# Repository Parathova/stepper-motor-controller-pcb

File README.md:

# stepper-motor-controller-pcb

## Overview

Designed a custom PCB in KiCad to control a NEMA-17
stepper motor through an A4988 driver.

The design includes:

- Arduino Uno headers
- A4988 driver interface
- Push-button inputs
- Status LEDs
- Power filtering capacitor
- Motor output connections

## Tools

- KiCad
- Arduino Uno
- A4988 Stepper Driver

## Features

- Controls NEMA-17 stepper motor
- Button-based user interface
- Modular driver design
- Custom PCB layout

## Schematic

## PCB Layout

## 3D Render

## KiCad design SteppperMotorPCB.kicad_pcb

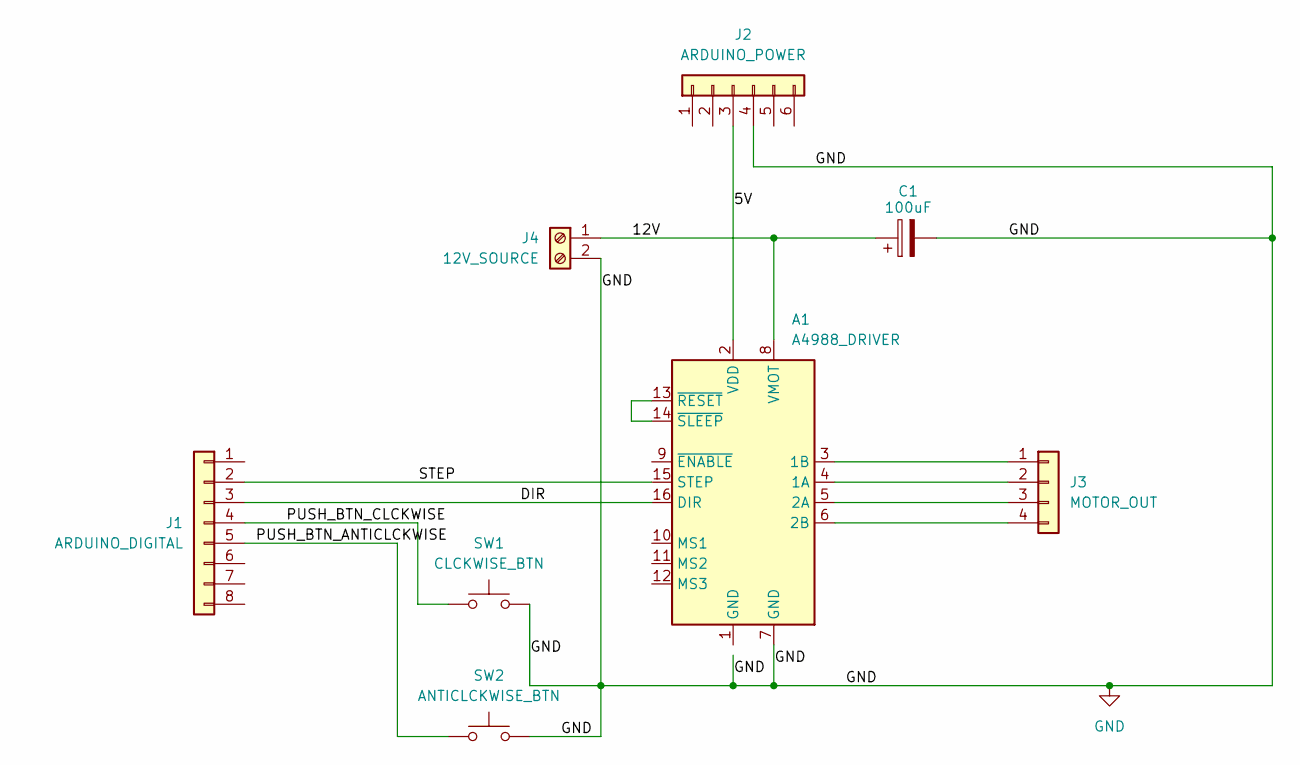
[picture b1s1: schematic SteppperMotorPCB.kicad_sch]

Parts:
A1: A4988_DRIVER; Pololu_Breakout-16_15.2x20.3mm
C1: 100uF; CP_Radial_D8.0mm_P3.50mm
J1: ARDUINO_DIGITAL; PinHeader_1x08_P2.54mm_Vertical
J2: ARDUINO_POWER; PinHeader_1x06_P2.54mm_Vertical
J3: MOTOR_OUT; PinHeader_1x04_P2.54mm_Vertical
J4: 12V_SOURCE; TerminalBlock_Phoenix_MKDS-1,5-2-5.08_1x02_P5.08mm_Horizont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
SW1: CLCKWISE_BTN; SW_PUSH_6mm
SW2: ANTICLCKWISE_BTN; SW_PUSH_6mm

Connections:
/5V: A1.2 (VDD), J2.3
/12V: A1.8 (VMOT), C1.1, J4.1
/DIR: A1.16 (DIR), J1.3
/PUSH_BTN_ANTICLCKWISE: J1.5, SW2.1
/PUSH_BTN_CLCKWISE: J1.4, SW1.1
/STEP: A1.15 (STEP), J1.2
GND: A1.7 (GND), C1.2, J2.4, J4.2, SW1.2, SW2.2
unnamed: A1.4 (1A), J3.2
unnamed: A1.3 (1B), J3.1
unnamed: A1.5 (2A), J3.3
unnamed: A1.6 (2B), J3.4
unnamed: A1.13 (~RESET), A1.14 (~SLEEP)

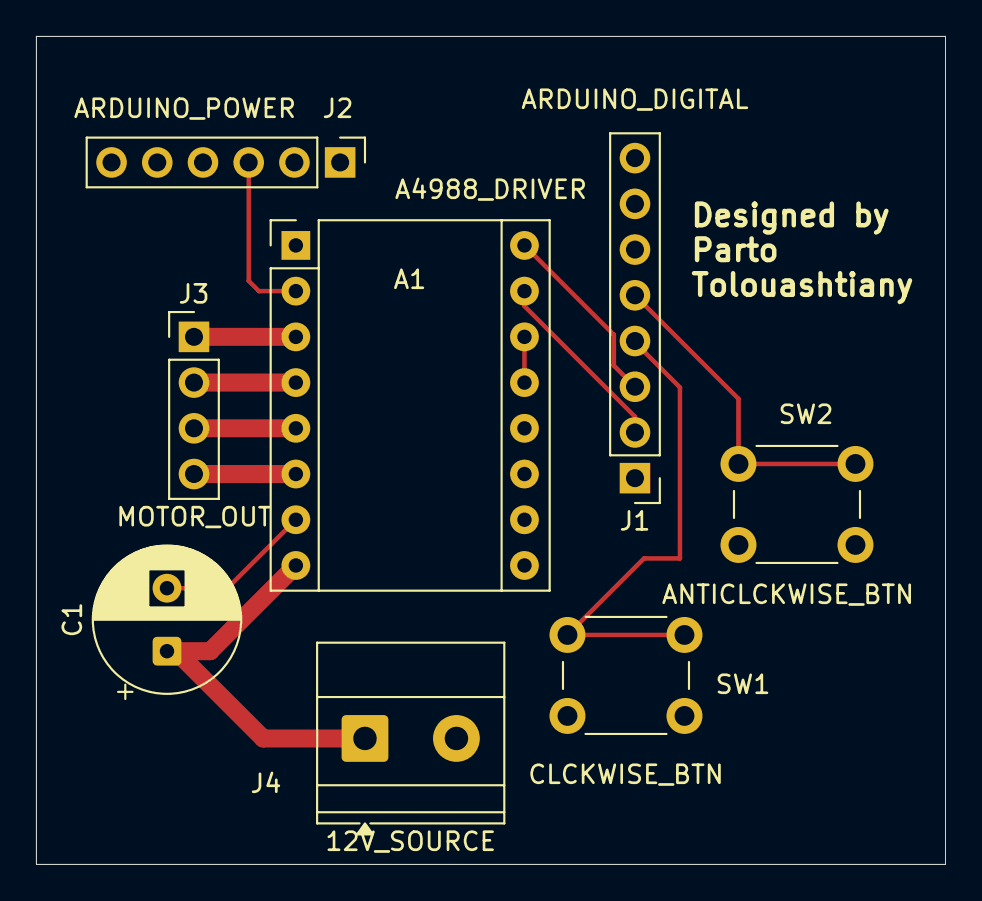
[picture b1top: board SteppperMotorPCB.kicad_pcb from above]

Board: 2 copper layers, 50.5 x 46.0 mm, 8 parts (0 on the bottom side), 12 nets.

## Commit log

2026-06-15 Enhance README with project details and images
    Added detailed project overview, tools used, features, and images of schematic, PCB layout, and 3D render.
